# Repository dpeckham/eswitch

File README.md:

# eswitch — eight-channel switching bank

**PROTO-PWR3: bare-board prototype fabrication release.** Shared LM74800-Q1
AUTO/logic protection, with passive raw-battery BYPASS selected by one movable
ATO fuse per channel. BYPASS disconnects the PROFET output and has no series
electronics. Move fuses only with power disconnected.

Open **[redesign/eswitch-simple.kicad_pro](redesign/eswitch-simple.kicad_pro)**.
The **212 × 116 mm**, four-layer ESP32-S3 board retains two banks of four channels
at 26 mm pitch and opposite output edges.

- **[JLCPCB upload ZIP](fab/eswitch-simple-jlcpcb-gerbers.zip)**
- [Order settings](redesign/JLCPCB-ORDER.txt) · [Build/assembly notes](redesign/BUILD.md)
- [Full fabrication package](fab/eswitch-simple-fabrication.zip)
- [Portable KiCad project](fab/eswitch-simple-project.zip)
- [One-board DigiKey upload](fab/eswitch-digikey-qty1.csv)
- [BOM](redesign/bom-draft.csv) · [Partial historical cost estimate](redesign/cost-estimate.json)
- [Top view](fab/board-top.png) · [Bottom view](fab/board-bottom.png)
- [Design overview](redesign/README.md) · [Engineering review](redesign/PROTECTION-REVIEW.md)

Native ERC, DRC, connectivity and schematic parity checks pass. The topology model
checks 52,488 mode/supply combinations and 54 isolation cases. Copper-width and
physical layer-transfer checks cover the shared protection and all channels.

This release permits making **first articles for controlled bench testing**.
40 A continuous operation, +80 V surge survival, pump transients and battery-fault
coordination require hardware validation. It is not an installation qualification.
Firmware is not supplied. Follow BUILD.md for initial current-limited testing.

```sh
just verify    # schematic, topology, saved PCB and copper checks
just package   # matched, checked fabrication/project ZIPs and BOM upload
just render    # current board views
```

Native KiCad is discovered on macOS; override with `KICAD_CLI`/`KICAD_PYTHON`.
`redesign/` is authoritative, `fab/` holds the release, `out/` holds disposable
checks and routing candidates. Earlier releases remain in Git history. Do not
order intermediate `out/redesign` boards. Component pricing is incomplete and
historical, not a current cart quote; F10 fasteners are separate purchases.

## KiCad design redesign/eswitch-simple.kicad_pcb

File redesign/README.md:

# Eight-channel eswitch — PROTO-PWR3

212 × 116 mm, four-layer prototype with shared LM74800-Q1 AUTO/logic protection
and unconditional passive fuse-selected BYPASS. Open `eswitch-simple.kicad_pro`.

The release is for **bare-board first articles and controlled bench testing**.
See [BUILD.md](BUILD.md) for assembly and ordering, and
[PROTECTION-REVIEW.md](PROTECTION-REVIEW.md) for the engineering review and
hardware tests. Neither 40 A continuous operation nor surge survival has been
qualified on hardware. Firmware is not supplied.

## Power paths

```
AUTO:   BATT_RAW -- F10 -- LM74800 cutoff -- shared VS -- PROFET -- ATO fuse -- LOAD
BYPASS: BATT_RAW ----------------------------------------------- ATO fuse -- LOAD
```

One movable ATO fuse per channel, three clips. Pins 1/2/3 are PROFET_OUT/LOAD/RAW.
Move the fuse between AUTO and BYPASS only with power disconnected; remove it for
OFF. BYPASS/OFF disconnects the load from the PROFET output, avoiding body-diode
backfeed. BYPASS has no series electronics and receives raw surges/reversed polarity.

For electronics-fault recovery, disconnect battery and USB, remove F10, move usable
channel fuses to BYPASS, then restore power. All AUTO channels may be lost; no extra
fixed per-channel fuses are required. Upstream-fuse selectivity and uninterrupted
operation are not promised. Shared copper/terminal damage is outside the model.

F10 is a removable Mersen FR14GG50V40 with two MR14SPRING clips and M5 terminals.
F9 remains the 2 A logic fuse. AUTO uses BTS7004 on CH1/2, BTS7008 on CH3–7 and
BTS7002 on CH8. Maximum ATO fuses: **10/10/5/5/5/5/5/20 A**. These are fuse maxima,
not validated continuous channel currents. LEDs show AUTO output voltage; BYPASS
current is not measured. J11–J18 pin 1 is LOAD+, pin 2 is GND. J5 is 3.3 V bench UART.

The common-source protection targets a +80 V, several-second input event using
overvoltage cutoff, not fuse operation or continuous linear clamping. Nominal cutoff
is 16.841 V. The four 200 V and two 60 V MOSFETs use individual gate resistors.
C27 is 1 µF for the parallel-bank charge pump. The existing sense resistance values
remain; R104–R804 use high-power ERJ-PA3 parts for fault-reporting dissipation.

## Verification and fabrication

- Native ERC, PCB DRC, unconnected and schematic-parity checks must all be zero.
- Topology model: 52,488 mode/supply combinations and 54 fault/removal cases.
- `power-copper-review.json`: 60 planar power paths with explicit regression floors.
- `power-transition-review.json`: real pad-layer connections and local via arrays.
- `protection-screen.json` and `sense-screen.json`: reproducible static screens.
- `out/redesign/verification.json`: source hashes and checks for the packaged revision.

The two-layer LOAD corridors, protected supply spine and raw BYPASS feed are
explicitly reserved before routing signals. Geometry checks are not thermal solvers.
Manufacturing uses JLC041622-3313, 2 oz inner and outer copper, filled/capped vias
and 90 Ω USB differential control. Follow `JLCPCB-ORDER.txt` exactly.

```
python3 redesign/generate.py  # explicitly regenerate schematic/BOM after changes
just verify                  # ERC/topology/parity/geometry/physical transitions
just package                 # verified fabrication and portable project ZIPs
just render                  # board views
```

The saved PCB is authoritative. Routing scripts and `out/redesign/protection-*`
files are development history, not alternative ordering files. Some intermediate
candidates intentionally contain errors or disconnected nets. Do not regenerate
placement over the finished board. KiCad's Python environment is required for
layout scripts; `requirements-route-gaps.txt` dependencies live in `out/py39`.

## Procurement and installation

`bom-draft.csv` is the fitted one-board BOM despite its historical filename.
`../fab/eswitch-digikey-qty1.csv` contains exact MPN/quantity upload rows, without
spares. F10 screws, washers and shims are separate mechanical purchases detailed
in BUILD.md. Stock and cart acceptance must be checked when ordering.

`cost-estimate.json` applies historical prices only where known and explicitly
lists unpriced parts. Its subtotal is **not a complete build price or current quote**.
Fabrication, assembly, hardware, shipping and taxes are excluded.

Intended installation: Vatrer 300 Ah LiFePO4, separate Victron Orion XS 12/12-70A
charger branch, 40 A MRBF eswitch feed and 75 A MRBF charger feed. Use 8 AWG copper
positive/negative for the 1 m battery run and 4 mm² positive/negative for the 3 m
pump run. CH1/2 with a provisional 10 A fuse is appropriate for the standard 12 V
Rule 1500 GPH model; confirm the actual pump. Direct-battery fault coordination,
thermal limits, pump transients and surge performance remain hardware tests.

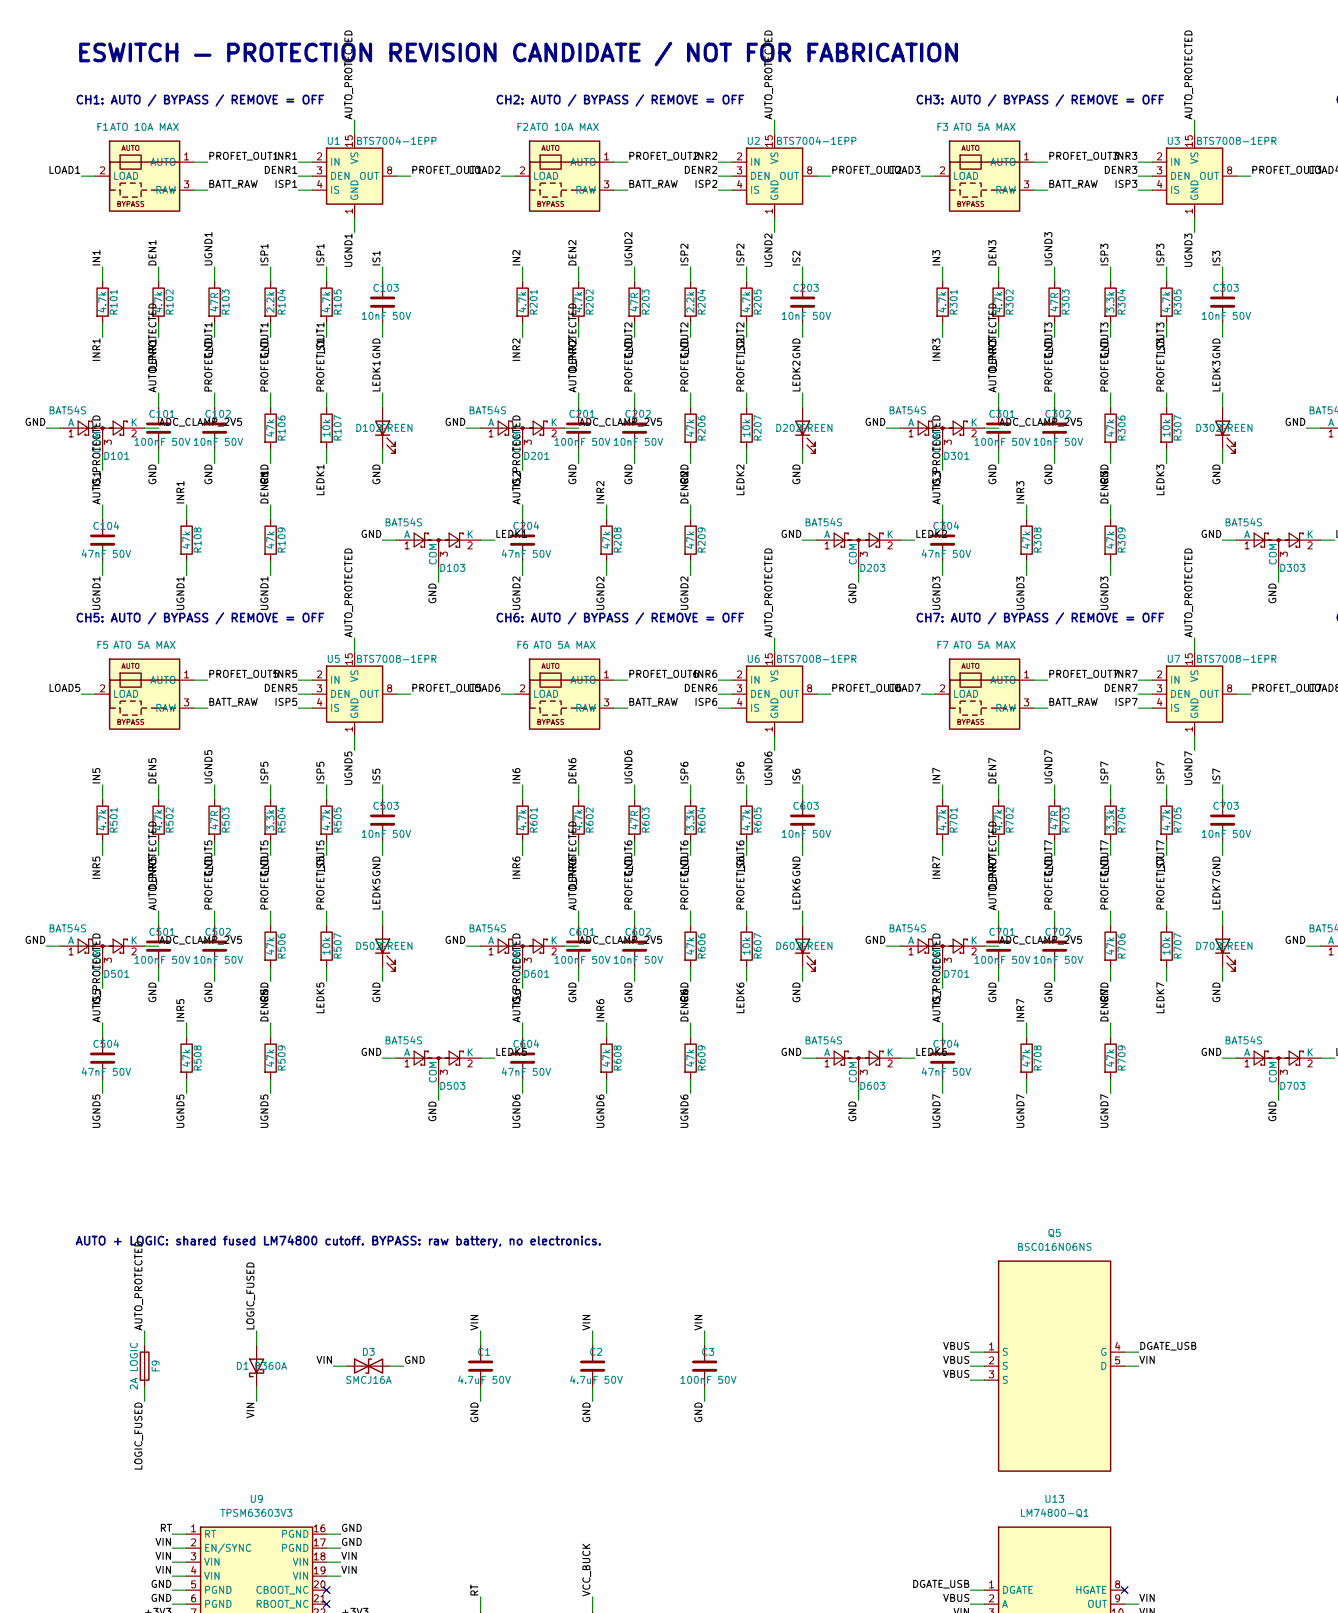
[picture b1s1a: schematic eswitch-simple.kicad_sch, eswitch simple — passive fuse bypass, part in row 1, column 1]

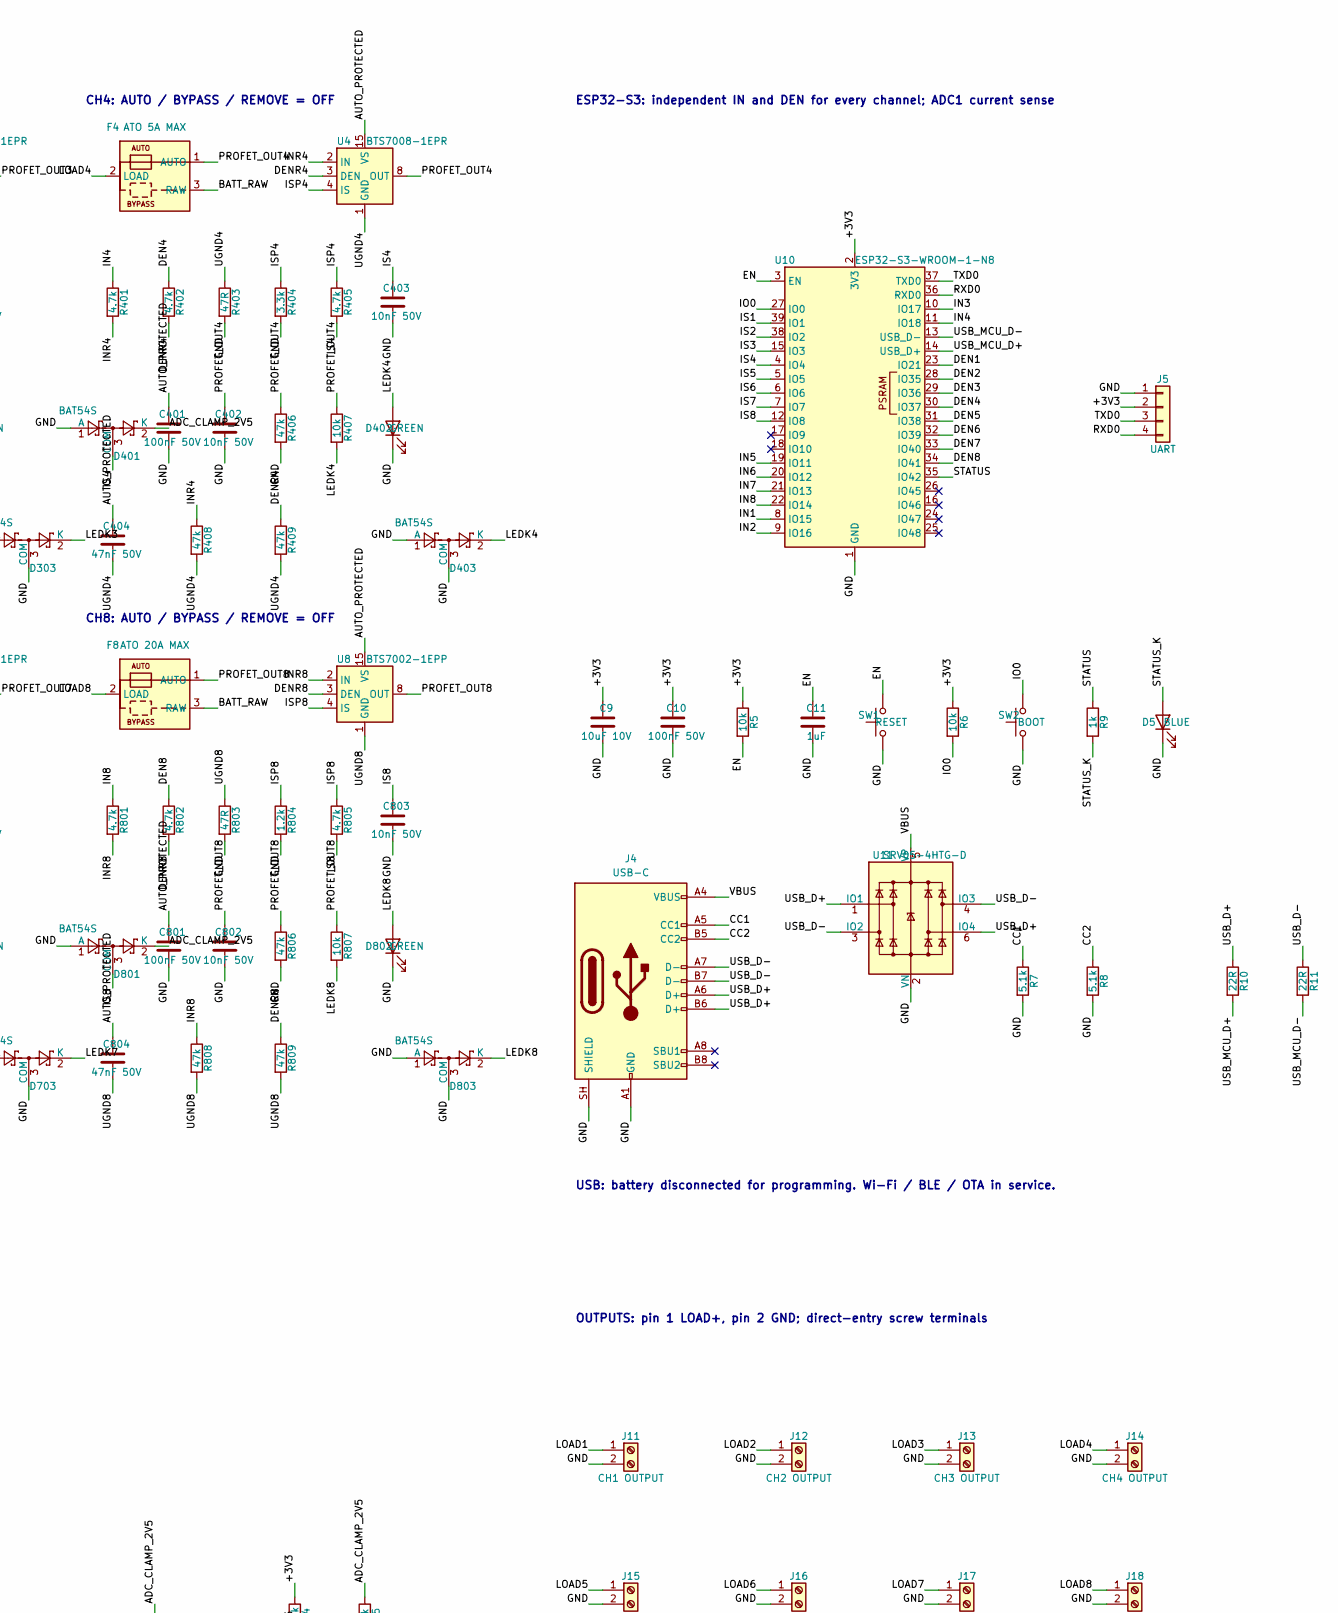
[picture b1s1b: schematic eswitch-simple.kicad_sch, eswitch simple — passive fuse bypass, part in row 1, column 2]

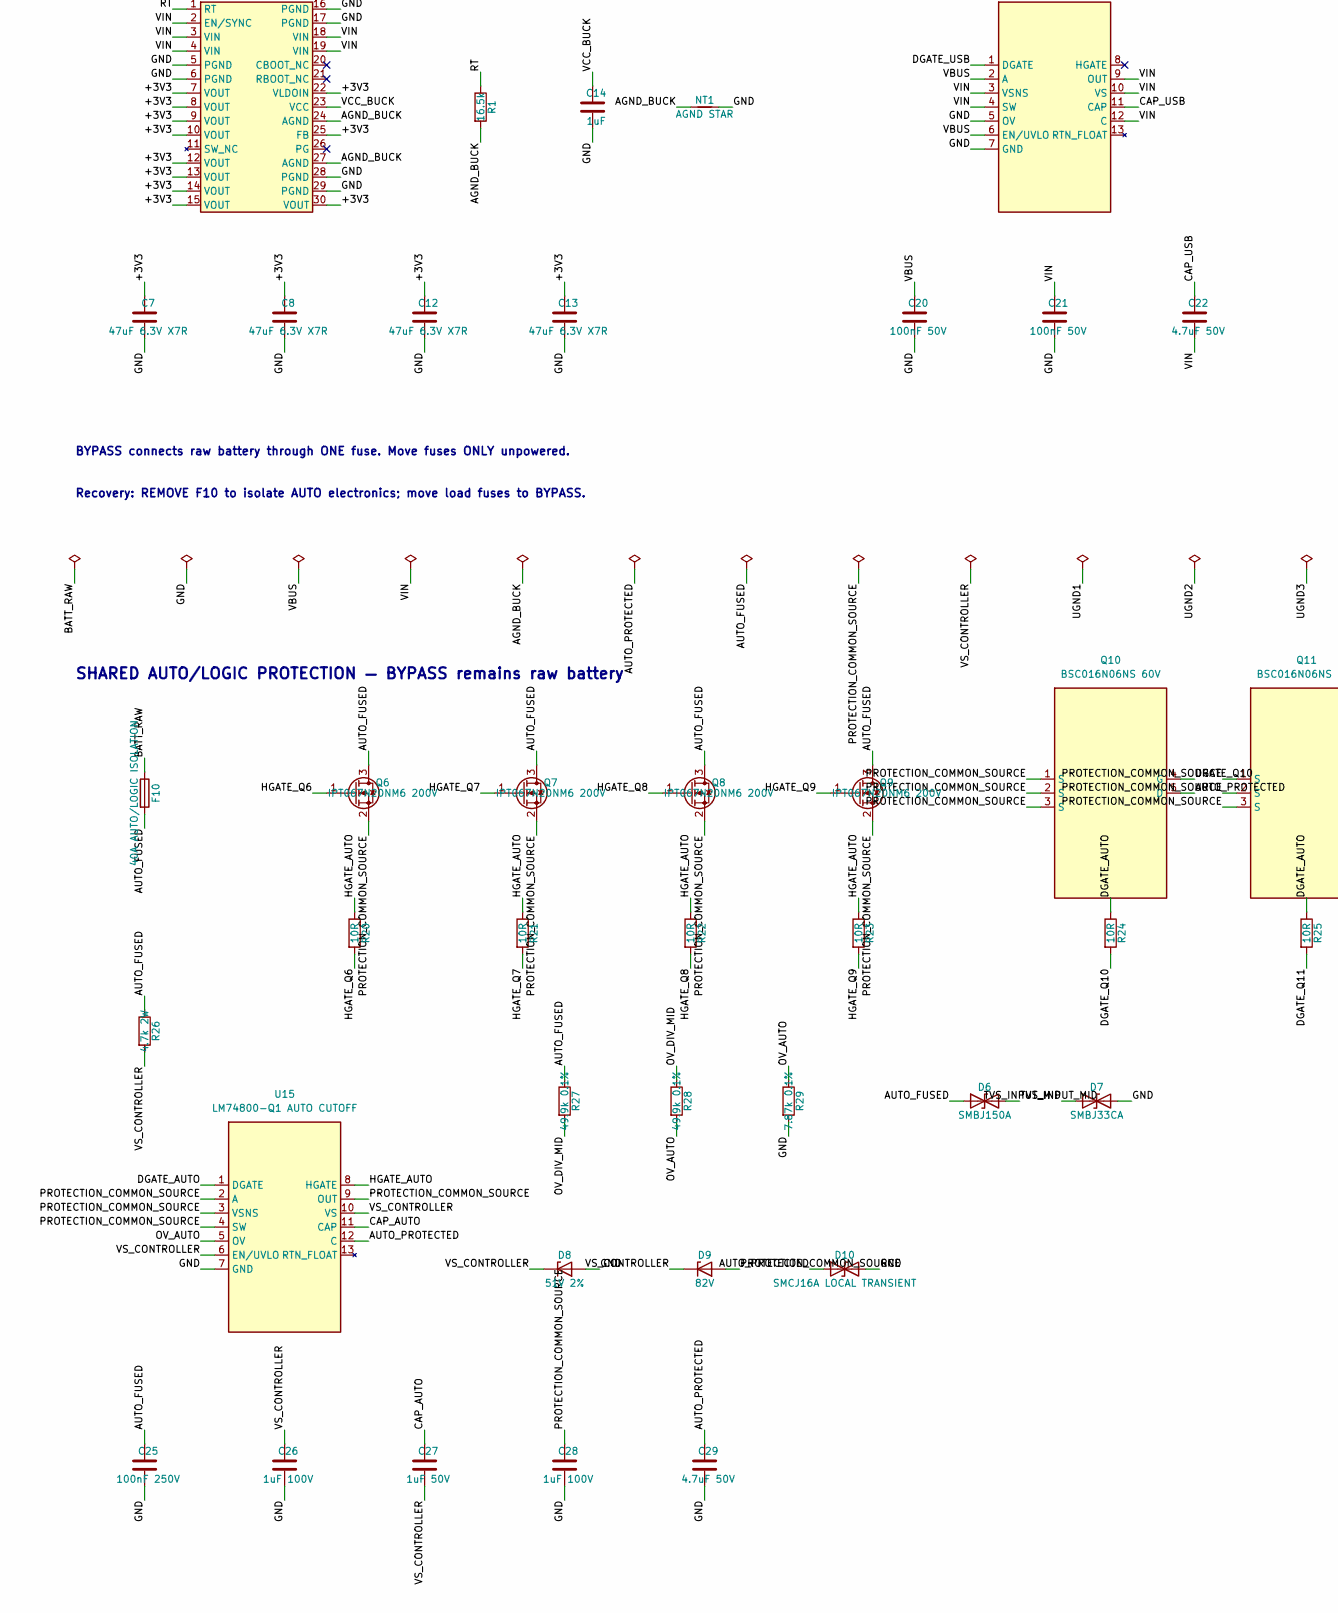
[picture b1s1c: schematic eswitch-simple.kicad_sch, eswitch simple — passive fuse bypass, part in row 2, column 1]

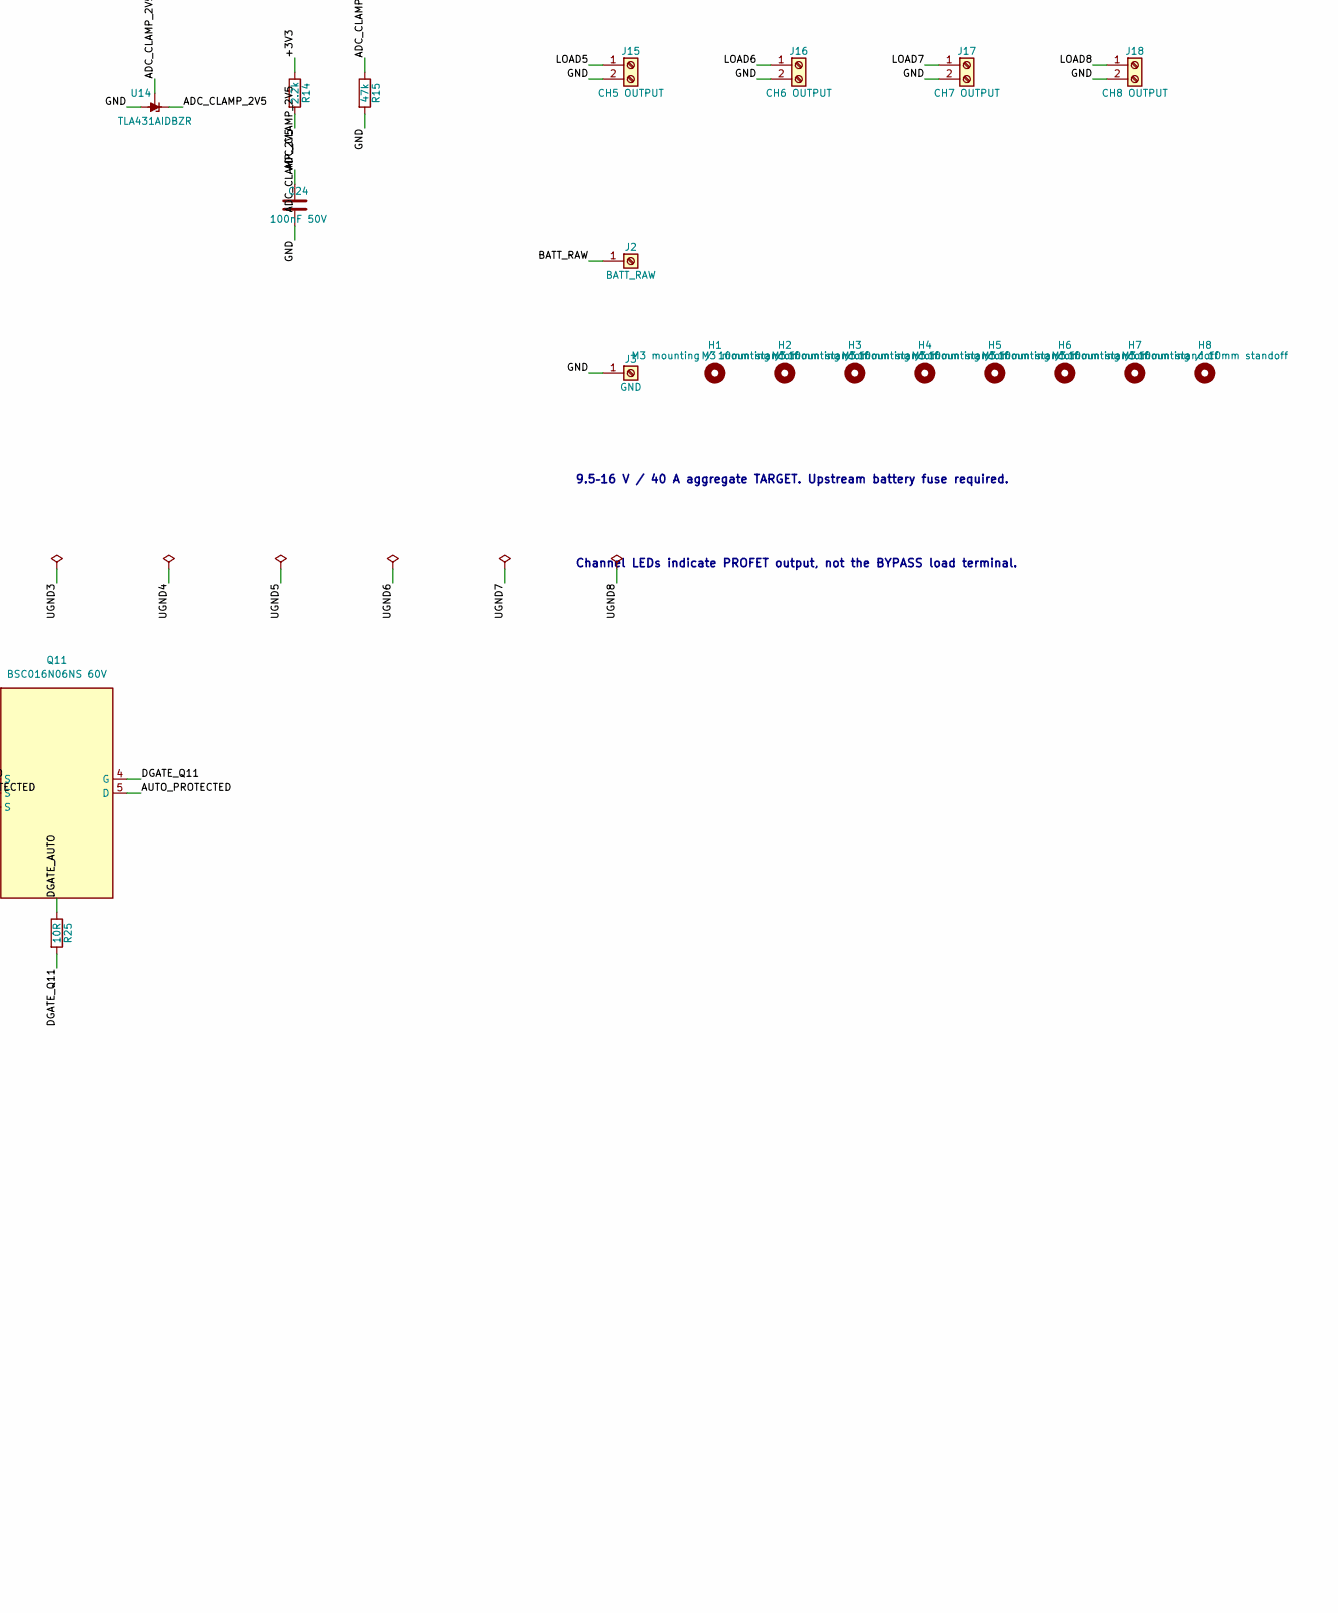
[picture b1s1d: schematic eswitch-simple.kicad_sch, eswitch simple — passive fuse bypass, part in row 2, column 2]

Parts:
C1, C2, C22, C29: 4.7uF 50V; C_1210_3225Metric; MPN GRM32ER71H475KA88L
C3, C10, C20, C21, C24, C101, C201, C301, C401, C501, C601, C701, C801: 100nF 50V; C_0805_2012Metric; MPN CL21B104KBCNNNC
C7, C8, C12, C13: 47uF 6.3V X7R; C_1210_3225Metric; MPN GCM32ER70J476KE19L
C9: 10uF 10V; C_0805_2012Metric; MPN CC0805KKX5R6BB106
C11, C14: 1uF; C_0603_1608Metric; MPN CC0603KRX7R7BB105
C25: 100nF 250V; C_1210_3225Metric; MPN C3225X7R2E104K200AA
C26, C28: 1uF 100V; C_1210_3225Metric; MPN GRM32CR72A105KA35L
C27: 1uF 50V; C_0805_2012Metric; MPN GRM21BR71H105KA12L
C102, C103, C202, C203, C302, C303, C402, C403, C502, C503, C602, C603, C702, C703, C802, C803: 10nF 50V; C_0805_2012Metric; MPN CL21B103KBANNNC
C104, C204, C304, C404, C504, C604, C704, C804: 47nF 50V; C_0805_2012Metric; MPN CL21B473KBCNNNC
D1: B360A; D_SMA; MPN B360A-13-F
D3: SMCJ16A; D_SMC; MPN SMCJ16A
D5: BLUE; LED_0603_1608Metric; MPN 150060BS75000
D6: SMBJ150A; D_SMB; MPN SMBJ150A
D7: SMBJ33CA; D_SMB; MPN SMBJ33CA
D8: 51V 2%; D_SMA; MPN BZG03B51-M3_A-08
D9: 82V; D_SMA; MPN BZG03C82-M3_A-08
D10: SMCJ16A LOCAL TRANSIENT; D_SMC; MPN SMCJ16A
D101, D103, D201, D203, D301, D303, D401, D403, D501, D503, D601, D603, D701, D703, D801, D803: BAT54S; SOT-23; MPN BAT54S-QR
D102, D202, D302, D402, D502, D602, D702, D802: GREEN; LED_0603_1608Metric; MPN 150060GS75000
F1, F2: ATO 10A MAX; Fuseholder_ATO_3pos_Keystone_3557; MPN 3557
F3, F4, F5, F6, F7: ATO 5A MAX; Fuseholder_ATO_3pos_Keystone_3557; MPN 3557
F8: ATO 20A MAX; Fuseholder_ATO_3pos_Keystone_3557; MPN 3557
F9: 2A LOGIC; Fuse_1206_3216Metric; MPN 0466002.NR
F10: 40A AUTO/LOGIC ISOLATION; Fuse_Mersen_14x51_MR14_Wuerth_M5; MPN FR14GG50V40
H1, H2, H3, H4, H5, H6, H7, H8: M3 mounting / 10mm standoff; MountingHole_3.2mm_M3; MPN R30-1001002
J2: BATT_RAW; ScrewTerminal_Wuerth_74650195_M5; MPN 74650195
J3: GND; ScrewTerminal_Wuerth_74650195_M5; MPN 74650195
J4: USB-C; USB4105_NPTH_0p2; MPN USB4105-GF-A
J5: UART; PinHeader_1x04_P2.54mm_Vertical; MPN 61300411121
J11: CH1 OUTPUT; TerminalBlock_1x02_P7.62mm_Wuerth_2184; MPN 691218410002
J12: CH2 OUTPUT; TerminalBlock_1x02_P7.62mm_Wuerth_2184; MPN 691218410002
J13: CH3 OUTPUT; TerminalBlock_1x02_P7.62mm_Wuerth_2184; MPN 691218410002
J14: CH4 OUTPUT; TerminalBlock_1x02_P7.62mm_Wuerth_2184; MPN 691218410002
J15: CH5 OUTPUT; TerminalBlock_1x02_P7.62mm_Wuerth_2184; MPN 691218410002
J16: CH6 OUTPUT; TerminalBlock_1x02_P7.62mm_Wuerth_2184; MPN 691218410002
J17: CH7 OUTPUT; TerminalBlock_1x02_P7.62mm_Wuerth_2184; MPN 691218410002
J18: CH8 OUTPUT; TerminalBlock_1x02_P7.62mm_Wuerth_2184; MPN 691218410002
NT1: AGND STAR; NetTie-2_SMD_Pad0.5mm
Q5: BSC016N06NS; Infineon_PG-TDSON-8_6.15x5.15mm; MPN BSC016N06NSATMA1
Q6, Q7, Q8, Q9: IPT067N20NM6 200V; Infineon_PG-HSOF-8-1; MPN IPT067N20NM6ATMA1
Q10, Q11: BSC016N06NS 60V; Infineon_PG-TDSON-8_6.15x5.15mm; MPN BSC016N06NSATMA1
R1: 16.5k; R_0603_1608Metric; MPN RC0603FR-0716K5L
R5, R6, R107, R207, R307, R407, R507, R607, R707, R807: 10k; R_0603_1608Metric; MPN RC0603FR-0710KL
R7, R8: 5.1k; R_0603_1608Metric; MPN ERJ-3EKF5101V
R9: 1k; R_0603_1608Metric; MPN RC0603FR-071KL
R10, R11: 22R; R_0603_1608Metric; MPN ERJ-3EKF22R0V
R14: 2.2k; R_0603_1608Metric; MPN RC0603FR-072K2L
R15, R106, R108, R109, R206, R208, R209, R306, R308, R309, R406, R408, R409, R506, R508, R509, R606, R608, R609, R706, R708, R709, R806, R808, R809: 47k; R_0603_1608Metric; MPN RC0603FR-0747KL
R20, R21, R22, R23, R24, R25: 10R; R_0805_2012Metric; MPN RC0805FR-0710RL
R26: 4.7k 2W; R_Axial_DIN0411_L9.9mm_D3.6mm_P15.24mm_Horizontal; MPN PR02000204701JA100
R27, R28: 49.9k 0.1%; R_0805_2012Metric; MPN RT0805BRD0749K9L
R29: 7.87k 0.1%; R_0805_2012Metric; MPN RT0805BRD077K87L
R101, R102, R105, R201, R202, R205, R301, R302, R305, R401, R402, R405, R501, R502, R505, R601, R602, R605, R701, R702, R705, R801, R802, R805: 4.7k; R_0603_1608Metric; MPN RC0603FR-074K7L
R103, R203, R303, R403, R503, R603, R703, R803: 47R; R_0805_2012Metric; MPN RC0805FR-0747RL
R104, R204: 2.2k; R_0603_1608Metric; MPN ERJ-PA3F2201V
R304, R404, R504, R604, R704: 3.3k; R_0603_1608Metric; MPN ERJ-PA3F3301V
R804: 1.2k; R_0603_1608Metric; MPN ERJ-PA3F1201V
SW1: RESET; SW_SPST_PTS645Sx43SMTR92; MPN PTS645SM43SMTR92 LFS
SW2: BOOT; SW_SPST_PTS645Sx43SMTR92; MPN PTS645SM43SMTR92 LFS
U1, U2: BTS7004-1EPP; Infineon_PG-TSDSO-14-22; MPN BTS70041EPPXUMA1
U3, U4, U5, U6, U7: BTS7008-1EPR; Infineon_PG-TSDSO-14-22; MPN BTS70081EPRXUMA1
U8: BTS7002-1EPP; Infineon_PG-TSDSO-14-22; MPN BTS70021EPPXUMA1
U9: TPSM63603V3; TI_RDH0030A_TPSM63603; MPN TPSM63603V3RDHR
U10: ESP32-S3-WROOM-1-N8; ESP32-S3-WROOM-1_Edge; MPN ESP32-S3-WROOM-1-N8
U11: SRV05-4HTG-D; SOT-23-6; MPN SRV05-4HTG-D
U13: LM74800-Q1; WSON-12-1EP_3x3mm_P0.5mm_EP1.5x2.5mm; MPN LM74800QDRRRQ1
U14: TLA431AIDBZR; SOT-23; MPN TLA431AIDBZR
U15: LM74800-Q1 AUTO CUTOFF; WSON-12-1EP_3x3mm_P0.5mm_EP1.5x2.5mm; MPN LM74800QDRRRQ1

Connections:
/+3V3: C7.1, C8.1, C9.1, C10.1, C12.1, C13.1, J5.2, R5.1, R6.1, R14.1, U9.7 (VOUT), U9.8 (VOUT), U9.9 (VOUT), U9.10 (VOUT), U9.12 (VOUT), U9.13 (VOUT), U9.14 (VOUT), U9.15 (VOUT), U9.22 (VLDOIN), U9.25 (FB), U9.30 (VOUT), U10.2 (3V3)
/ADC_CLAMP_2V5: C24.1, D101.2 (K), D201.2 (K), D301.2 (K), D401.2 (K), D501.2 (K), D601.2 (K), D701.2 (K), D801.2 (K), R14.2, R15.1, U14.1 (K), U14.2 (REF)
/AGND_BUCK: NT1.1, R1.2, U9.24 (AGND), U9.27 (AGND)
/AUTO_FUSED: C25.1, D6.1 (A1), F10.2, Q6.3 (D), Q7.3 (D), Q8.3 (D), Q9.3 (D), R26.1, R27.1
/AUTO_PROTECTED: C29.1, C101.1, C104.1, C201.1, C204.1, C301.1, C304.1, C401.1, C404.1, C501.1, C504.1, C601.1, C604.1, C701.1, C704.1, C801.1, C804.1, D10.1 (A1), F9.1, Q10.5 (D), Q11.5 (D), U1.15 (VS), U2.15 (VS), U3.15 (VS), U4.15 (VS), U5.15 (VS), U6.15 (VS), U7.15 (VS), U8.15 (VS), U15.12 (C)
/BATT_RAW: F1.3 (RAW), F2.3 (RAW), F3.3 (RAW), F4.3 (RAW), F5.3 (RAW), F6.3 (RAW), F7.3 (RAW), F8.3 (RAW), F10.1, J2.1
/CAP_AUTO: C27.1, U15.11 (CAP)
/CAP_USB: C22.1, U13.11 (CAP)
/CC1: J4.A5 (CC1), R7.1
/CC2: J4.B5 (CC2), R8.1
/DEN1: R102.1, U10.23 (IO21)
/DEN2: R202.1, U10.28 (IO35)
/DEN3: R302.1, U10.29 (IO36)
/DEN4: R402.1, U10.30 (IO37)
/DEN5: R502.1, U10.31 (IO38)
/DEN6: R602.1, U10.32 (IO39)
/DEN7: R702.1, U10.33 (IO40)
/DEN8: R802.1, U10.34 (IO41)
/DENR1: R102.2, R109.1, U1.3 (DEN)
/DENR2: R202.2, R209.1, U2.3 (DEN)
/DENR3: R302.2, R309.1, U3.3 (DEN)
/DENR4: R402.2, R409.1, U4.3 (DEN)
/DENR5: R502.2, R509.1, U5.3 (DEN)
/DENR6: R602.2, R609.1, U6.3 (DEN)
/DENR7: R702.2, R709.1, U7.3 (DEN)
/DENR8: R802.2, R809.1, U8.3 (DEN)
/DGATE_AUTO: R24.1, R25.1, U15.1 (DGATE)
/DGATE_Q10: Q10.4 (G), R24.2
/DGATE_Q11: Q11.4 (G), R25.2
/DGATE_USB: Q5.4 (G), U13.1 (DGATE)
/EN: C11.1, R5.2, SW1.2, U10.3 (EN)
/GND: C1.2, C2.2, C3.2, C7.2, C8.2, C9.2, C10.2, C11.2, C12.2, C13.2, C14.2, C20.2, C21.2, C24.2, C25.2, C26.2, C28.2, C29.2, C101.2, C102.2, C103.2, C201.2, C202.2, C203.2, C301.2, C302.2, C303.2, C401.2, C402.2, C403.2, C501.2, C502.2, C503.2, C601.2, C602.2, C603.2, C701.2, C702.2, C703.2, C801.2, C802.2, C803.2, D3.2 (A2), D5.1 (K), D7.2 (A2), D8.2 (A), D10.2 (A2), D101.1 (A), D102.1 (K), D103.1 (A), D103.3 (COM), D201.1 (A), D202.1 (K), D203.1 (A), D203.3 (COM), D301.1 (A), D302.1 (K), D303.1 (A), D303.3 (COM), D401.1 (A), D402.1 (K), D403.1 (A), D403.3 (COM), D501.1 (A), D502.1 (K), D503.1 (A), D503.3 (COM), D601.1 (A), D602.1 (K), D603.1 (A), D603.3 (COM), D701.1 (A), D702.1 (K), D703.1 (A), D703.3 (COM), D801.1 (A), D802.1 (K), D803.1 (A), D803.3 (COM), J3.1, J4.A1 (GND), J4.A12 (GND), J4.B1 (GND), J4.B12 (GND), J4.SH (SHIELD), J5.1, J11.2, J12.2, J13.2, J14.2, J15.2, J16.2, J17.2, J18.2, NT1.2, R7.2, R8.2, R15.2, R29.2, R103.2, R104.2, R106.2, R203.2, R204.2, R206.2, R303.2, R304.2, R306.2, R403.2, R404.2, R406.2, R503.2, R504.2, R506.2, R603.2, R604.2, R606.2, R703.2, R704.2, R706.2, R803.2, R804.2, R806.2, SW1.1, SW2.1, U9.5 (PGND), U9.6 (PGND), U9.16 (PGND), U9.17 (PGND), U9.28 (PGND), U9.29 (PGND), U10.1 (GND), U10.40 (GND), U10.41 (GND), U11.2 (VN), U13.5 (OV), U13.7 (GND), U14.3 (A), U15.7 (GND)
/HGATE_AUTO: R20.1, R21.1, R22.1, R23.1, U15.8 (HGATE)
/HGATE_Q6: Q6.1 (G), R20.2
/HGATE_Q7: Q7.1 (G), R21.2
/HGATE_Q8: Q8.1 (G), R22.2
/HGATE_Q9: Q9.1 (G), R23.2
/IN1: R101.1, U10.8 (IO15)
/IN2: R201.1, U10.9 (IO16)
/IN3: R301.1, U10.10 (IO17)
/IN4: R401.1, U10.11 (IO18)
/IN5: R501.1, U10.19 (IO11)
/IN6: R601.1, U10.20 (IO12)
/IN7: R701.1, U10.21 (IO13)
/IN8: R801.1, U10.22 (IO14)
/INR1: R101.2, R108.1, U1.2 (IN)
/INR2: R201.2, R208.1, U2.2 (IN)
/INR3: R301.2, R308.1, U3.2 (IN)
/INR4: R401.2, R408.1, U4.2 (IN)
/INR5: R501.2, R508.1, U5.2 (IN)
/INR6: R601.2, R608.1, U6.2 (IN)
/INR7: R701.2, R708.1, U7.2 (IN)
/INR8: R801.2, R808.1, U8.2 (IN)
/IO0: R6.2, SW2.2, U10.27 (IO0)
/IS1: C103.1, D101.3 (COM), R105.2, U10.39 (IO1)
/IS2: C203.1, D201.3 (COM), R205.2, U10.38 (IO2)
/IS3: C303.1, D301.3 (COM), R305.2, U10.15 (IO3)
/IS4: C403.1, D401.3 (COM), R405.2, U10.4 (IO4)
/IS5: C503.1, D501.3 (COM), R505.2, U10.5 (IO5)
/IS6: C603.1, D601.3 (COM), R605.2, U10.6 (IO6)
/IS7: C703.1, D701.3 (COM), R705.2, U10.7 (IO7)
/IS8: C803.1, D801.3 (COM), R805.2, U10.12 (IO8)
/ISP1: R104.1, R105.1, U1.4 (IS)
/ISP2: R204.1, R205.1, U2.4 (IS)
/ISP3: R304.1, R305.1, U3.4 (IS)
/ISP4: R404.1, R405.1, U4.4 (IS)
/ISP5: R504.1, R505.1, U5.4 (IS)
/ISP6: R604.1, R605.1, U6.4 (IS)
/ISP7: R704.1, R705.1, U7.4 (IS)
/ISP8: R804.1, R805.1, U8.4 (IS)
/LEDK1: D102.2 (A), D103.2 (K), R107.2
/LEDK2: D202.2 (A), D203.2 (K), R207.2
/LEDK3: D302.2 (A), D303.2 (K), R307.2
/LEDK4: D402.2 (A), D403.2 (K), R407.2
/LEDK5: D502.2 (A), D503.2 (K), R507.2
/LEDK6: D602.2 (A), D603.2 (K), R607.2
/LEDK7: D702.2 (A), D703.2 (K), R707.2
/LEDK8: D802.2 (A), D803.2 (K), R807.2
/LOAD1: F1.2 (LOAD), J11.1
/LOAD2: F2.2 (LOAD), J12.1
/LOAD3: F3.2 (LOAD), J13.1
/LOAD4: F4.2 (LOAD), J14.1
/LOAD5: F5.2 (LOAD), J15.1
/LOAD6: F6.2 (LOAD), J16.1
/LOAD7: F7.2 (LOAD), J17.1
/LOAD8: F8.2 (LOAD), J18.1
/LOGIC_FUSED: D1.2 (A), F9.2
/OV_AUTO: R28.2, R29.1, U15.5 (OV)
/OV_DIV_MID: R27.2, R28.1
/PROFET_OUT1: C102.1, F1.1 (AUTO), R106.1, R107.1, U1.8 (OUT), U1.9 (OUT), U1.10 (OUT), U1.12 (OUT), U1.13 (OUT), U1.14 (OUT)
/PROFET_OUT2: C202.1, F2.1 (AUTO), R206.1, R207.1, U2.8 (OUT), U2.9 (OUT), U2.10 (OUT), U2.12 (OUT), U2.13 (OUT), U2.14 (OUT)
/PROFET_OUT3: C302.1, F3.1 (AUTO), R306.1, R307.1, U3.8 (OUT), U3.9 (OUT), U3.10 (OUT), U3.12 (OUT), U3.13 (OUT), U3.14 (OUT)
/PROFET_OUT4: C402.1, F4.1 (AUTO), R406.1, R407.1, U4.8 (OUT), U4.9 (OUT), U4.10 (OUT), U4.12 (OUT), U4.13 (OUT), U4.14 (OUT)
/PROFET_OUT5: C502.1, F5.1 (AUTO), R506.1, R507.1, U5.8 (OUT), U5.9 (OUT), U5.10 (OUT), U5.12 (OUT), U5.13 (OUT), U5.14 (OUT)
/PROFET_OUT6: C602.1, F6.1 (AUTO), R606.1, R607.1, U6.8 (OUT), U6.9 (OUT), U6.10 (OUT), U6.12 (OUT), U6.13 (OUT), U6.14 (OUT)
/PROFET_OUT7: C702.1, F7.1 (AUTO), R706.1, R707.1, U7.8 (OUT), U7.9 (OUT), U7.10 (OUT), U7.12 (OUT), U7.13 (OUT), U7.14 (OUT)
/PROFET_OUT8: C802.1, F8.1 (AUTO), R806.1, R807.1, U8.8 (OUT), U8.9 (OUT), U8.10 (OUT), U8.12 (OUT), U8.13 (OUT), U8.14 (OUT)
/PROTECTION_COMMON_SOURCE: C28.1, D9.2 (A), Q6.2 (S), Q7.2 (S), Q8.2 (S), Q9.2 (S), Q10.1 (S), Q10.2 (S), Q10.3 (S), Q11.1 (S), Q11.2 (S), Q11.3 (S), U15.2 (A), U15.3 (VSNS), U15.4 (SW), U15.9 (OUT)
/RT: R1.1, U9.1 (RT)
/RXD0: J5.4, U10.36 (RXD0)
/STATUS: R9.1, U10.35 (IO42)
/STATUS_K: D5.2 (A), R9.2
/TVS_INPUT_MID: D6.2 (A2), D7.1 (A1)
/TXD0: J5.3, U10.37 (TXD0)
/UGND1: C104.2, R103.1, R108.2, R109.2, U1.1 (GND)
/UGND2: C204.2, R203.1, R208.2, R209.2, U2.1 (GND)
/UGND3: C304.2, R303.1, R308.2, R309.2, U3.1 (GND)
/UGND4: C404.2, R403.1, R408.2, R409.2, U4.1 (GND)
/UGND5: C504.2, R503.1, R508.2, R509.2, U5.1 (GND)
/UGND6: C604.2, R603.1, R608.2, R609.2, U6.1 (GND)
/UGND7: C704.2, R703.1, R708.2, R709.2, U7.1 (GND)
/UGND8: C804.2, R803.1, R808.2, R809.2, U8.1 (GND)
/USB_D+: J4.A6 (D+), J4.B6 (D+), R10.1, U11.1 (IO1), U11.6 (IO4)
/USB_D-: J4.A7 (D-), J4.B7 (D-), R11.1, U11.3 (IO2), U11.4 (IO3)
/USB_MCU_D+: R10.2, U10.14 (USB_D+)
/USB_MCU_D-: R11.2, U10.13 (USB_D-)
/VBUS: C20.1, J4.A4 (VBUS), J4.A9 (VBUS), J4.B4 (VBUS), J4.B9 (VBUS), Q5.1 (S), Q5.2 (S), Q5.3 (S), U11.5 (VP), U13.2 (A), U13.6 (EN/UVLO)
/VCC_BUCK: C14.1, U9.23 (VCC)
/VIN: C1.1, C2.1, C3.1, C21.1, C22.2, D1.1 (K), D3.1 (A1), Q5.5 (D), U9.2 (EN/SYNC), U9.3 (VIN), U9.4 (VIN), U9.18 (VIN), U9.19 (VIN), U13.3 (VSNS), U13.4 (SW), U13.9 (OUT), U13.10 (VS), U13.12 (C)
/VS_CONTROLLER: C26.1, C27.2, D8.1 (K), D9.1 (K), R26.2, U15.6 (EN/UVLO), U15.10 (VS)

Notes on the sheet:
ESWITCH — PROTECTION REVISION CANDIDATE / NOT FOR FABRICATION
ESP32-S3: independent IN and DEN for every channel; ADC1 current sense
USB: battery disconnected for programming. Wi-Fi / BLE / OTA in service.
AUTO + LOGIC: shared fused LM74800 cutoff. BYPASS: raw battery, no electronics.
OUTPUTS: pin 1 LOAD+, pin 2 GND; direct-entry screw terminals
9.5–16 V / 40 A aggregate TARGET. Upstream battery fuse required.
BYPASS connects raw battery through ONE fuse. Move fuses ONLY unpowered.
Recovery: REMOVE F10 to isolate AUTO electronics; move load fuses to BYPASS.
SHARED AUTO/LOGIC PROTECTION — BYPASS remains raw battery
Channel LEDs indicate PROFET output, not the BYPASS load terminal.
CH1: AUTO / BYPASS / REMOVE = OFF
CH2: AUTO / BYPASS / REMOVE = OFF
CH3: AUTO / BYPASS / REMOVE = OFF
CH4: AUTO / BYPASS / REMOVE = OFF
CH5: AUTO / BYPASS / REMOVE = OFF
CH6: AUTO / BYPASS / REMOVE = OFF
CH7: AUTO / BYPASS / REMOVE = OFF
CH8: AUTO / BYPASS / REMOVE = OFF

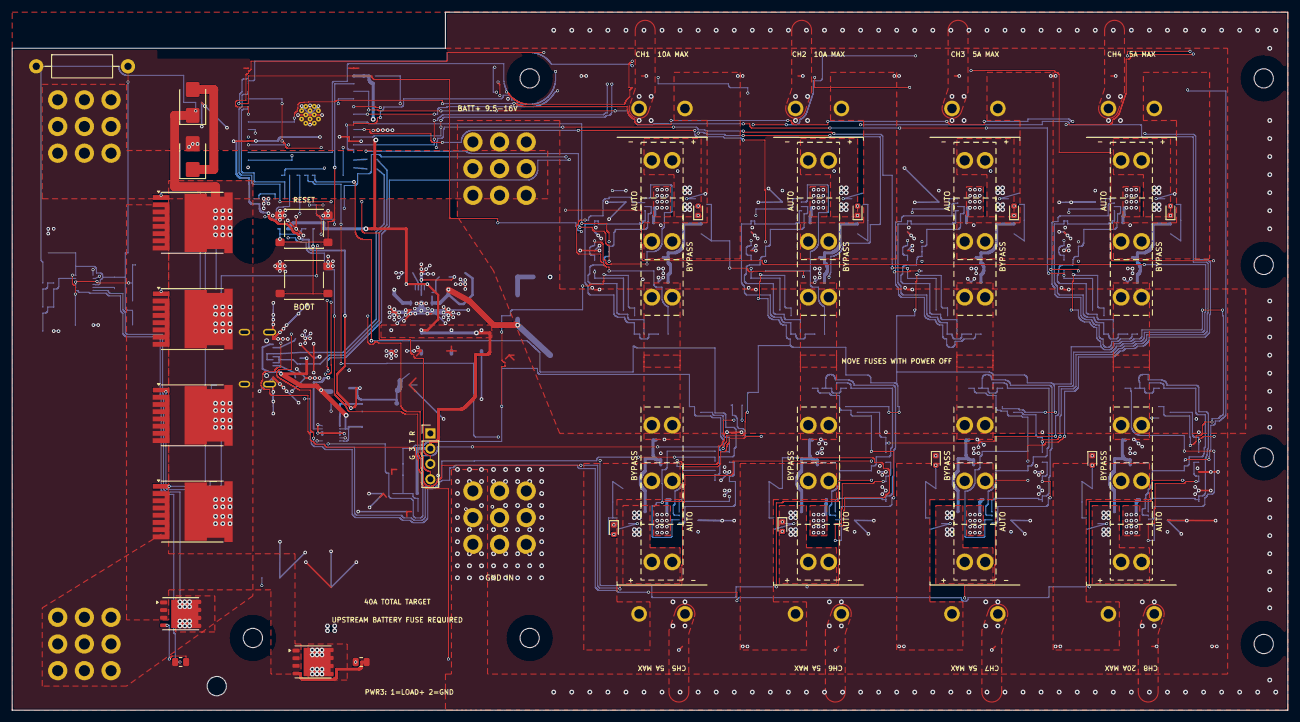
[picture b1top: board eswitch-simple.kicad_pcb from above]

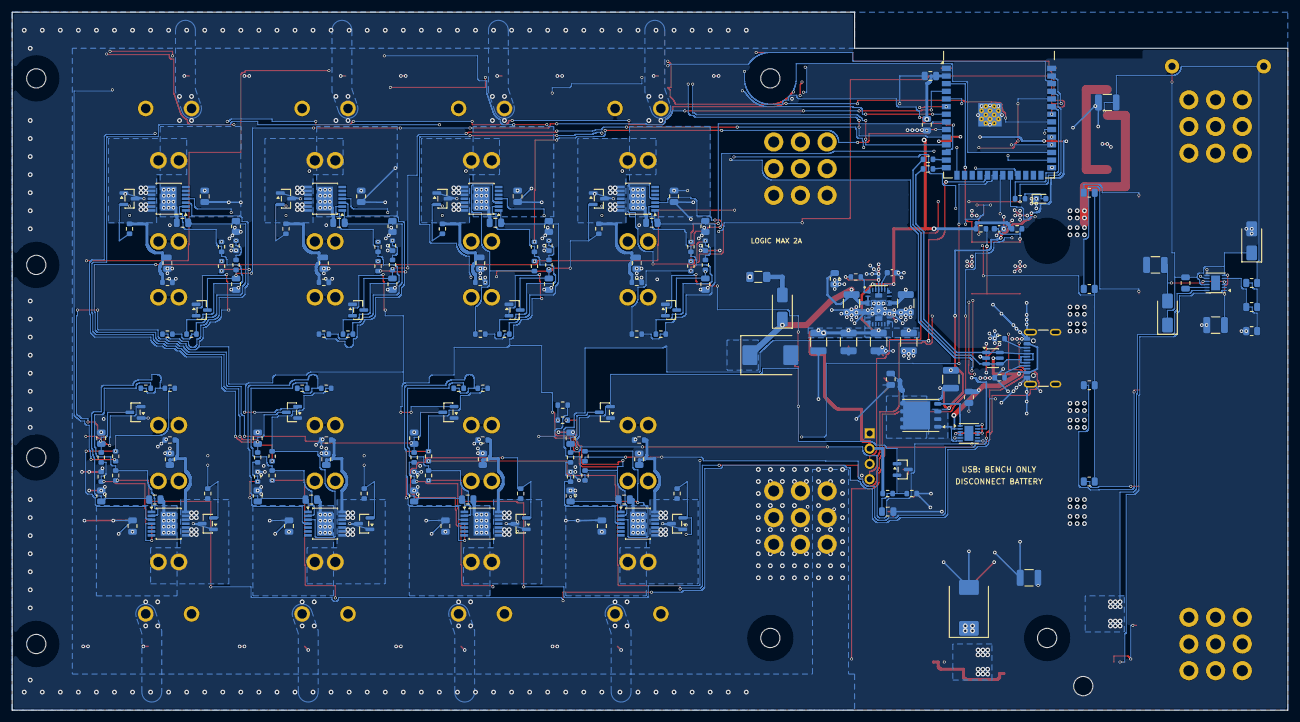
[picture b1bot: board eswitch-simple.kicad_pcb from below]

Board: 4 copper layers, 212.0 x 116.0 mm, 230 parts (181 on the bottom side), 120 nets.

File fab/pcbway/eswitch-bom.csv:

Item #,Designator,Qty,Manufacturer,Mfg Part #,Description / Value,Package/Footprint,Type,Your Instructions / Notes
1,"C1,C2",2,Murata,GRM32ER71H475KA88L,4.7uF 50V,1210,SMD,
2,C3,1,Samsung Electro-Mechanics,CL10B104KB8NNNC,100nF 50V,0603,SMD,
3,C4,1,Samsung Electro-Mechanics,CL10B104KB8NNNC,100nF 25V,0603,SMD,
4,C5,1,Samsung Electro-Mechanics,CL10B273KB8NNNC,27nF,0603,SMD,
5,C6,1,Samsung Electro-Mechanics,CL10C151JB8NNNC,150pF,0603,SMD,
6,"C7,C8",2,Murata,GRM32ER71A226KE20L,22uF 10V,1210,SMD,
7,C9,1,Samsung Electro-Mechanics,CL21A106KPFNNNE,10uF 10V,0805,SMD,
8,C10,1,Samsung Electro-Mechanics,CL10B104KB8NNNC,100nF,0603,SMD,
9,C11,1,Samsung Electro-Mechanics,CL10B105KO8NNNC,1uF,0603,SMD,
10,"C101,C201,C301,C401,C501,C601,C701,C801",8,Samsung Electro-Mechanics,CL21B104KBCNNNC,100nF 50V,0805,SMD,CVS
11,"C102,C202,C302,C402,C502,C602,C702,C802",8,Samsung Electro-Mechanics,CL21B103KBANNNC,10nF 50V,0805,SMD,COUT
12,"C103,C203,C303,C403,C503,C603,C703,C803",8,Samsung Electro-Mechanics,CL10C221JB8NNNC,220pF 50V,0603,SMD,CSENSE
13,"D1,D2,D4",3,Diodes Incorporated,B360-13-F,SS36,SMA,SMD,"12V -> VIN,USB -> VIN,catch diode"
14,D3,1,Littelfuse,SMBJ26A,SMBJ26A,SMB,SMD,bus TVS
15,D5,1,Wurth Elektronik,150060BS75000,BLUE,LED_0603,SMD,status LED IO41
16,"D101,D201,D301,D401,D501,D601,D701,D801",8,Nexperia,"BAT54S,215",BAT54S,SOT-23,SMD,ADC clamp
17,"D102,D202,D302,D402,D502,D602,D702,D802",8,Wurth Elektronik,150060GS75000,GREEN,LED_0603,SMD,load ON indicator
18,"F1,F2",2,Keystone Electronics,3557,ATO 10A,Fuseholder_ATO_3pos_Keystone_3557,Through-hole,"3 clips per position; CH1 10 A; AUTO: fuse in COM-SW; BYPASS: fuse in COM-LOAD,3 clips per position; CH2 10 A; AUTO: fuse in COM-SW; BYPASS: fuse in COM-LOAD"
19,"F3,F4,F5,F6,F7",5,Keystone Electronics,3557,ATO 5A,Fuseholder_ATO_3pos_Keystone_3557,Through-hole,"3 clips per position; CH3 5 A; AUTO: fuse in COM-SW; BYPASS: fuse in COM-LOAD,3 clips per position; CH4 5 A; AUTO: fuse in COM-SW; BYPASS: fuse in COM-LOAD,3 clips per position; CH5 5 A; AUTO: fuse in COM-SW; BYPASS: fuse in COM-LOAD,3 clips per position; CH6 5 A; AUTO: fuse in COM-SW; BYPASS: fuse in COM-LOAD,3 clips per position; CH7 5 A; AUTO: fuse in COM-SW; BYPASS: fuse in COM-LOAD"
20,F8,1,Keystone Electronics,3557,ATO 20A,Fuseholder_ATO_3pos_Keystone_3557,Through-hole,3 clips per position; CH8 20 A; AUTO: fuse in COM-SW; BYPASS: fuse in COM-LOAD
21,F9,1,Littelfuse,0466002.NR,2A 1206,1206,SMD,logic supply fuse
22,"H1,H2,H3,H4",4,,,M3,MountingHole_3.2mm_M3,Through-hole,
23,J1,1,Wurth Elektronik,691311400116,Wuerth 691311400116,TerminalBlock_1x16_P7.62mm_Wuerth_3114,Through-hole,"odd pins = GND, even pins = LOAD+"
24,J2,1,Keystone Electronics,8196,+12V IN,ScrewTerminal_Keystone_8196_10-32,Through-hole,
25,J3,1,Keystone Electronics,8196,GND IN,ScrewTerminal_Keystone_8196_10-32,Through-hole,
26,J4,1,GCT,USB4105-GF-A,USB-C,USB_C_Receptacle_GCT_USB4105-xx-A_16P_TopMnt_Horizontal,SMD,
27,J5,1,Wurth Elektronik,61300411121,UART,PinHeader_1x04_P2.54mm_Vertical,Through-hole,GND 3V3 TX RX
28,L1,1,Bourns,SRP7028A-100M,10uH 4A,L_Bourns_SRP7028A_7.3x6.6mm,SMD,
29,R1,1,YAGEO,RC0603FR-07200KL,200k 1%,0603,SMD,fsw 500 kHz
30,R2,1,YAGEO,RC0603FR-0731K6L,31.6k 1%,0603,SMD,
31,R3,1,YAGEO,RC0603FR-0710K2L,10.2k 1%,0603,SMD,
32,R4,1,YAGEO,RC0603FR-073K9L,3.9k,0603,SMD,
33,"R5,R6",2,YAGEO,RC0603FR-0710KL,10k,0603,SMD,
34,"R7,R8",2,YAGEO,RC0603FR-075K1L,5.1k,0603,SMD,
35,R9,1,YAGEO,RC0603FR-071KL,1k,0603,SMD,
36,"R101,R102,R105,R201,R202,R205,R301,R302,R305,R401,R402,R405,R501,R502,R505,R601,R602,R605,R701,R702,R705,R801,R802,R805",24,YAGEO,RC0603FR-074K7L,4.7k,0603,SMD,"RADC,RDEN,RIN"
37,"R103,R203,R303,R403,R503,R603,R703,R803",8,YAGEO,RC0805FR-0747RL,47R,0805,SMD,RGND (ReverseON)
38,"R104,R204",2,YAGEO,RC0603FR-072K2L,2.2k 1%,0603,SMD,RSENSE
39,"R106,R206,R306,R406,R506,R606,R706,R806",8,YAGEO,RC0603FR-0747KL,47k,0603,SMD,RPD
40,"R107,R207,R307,R407,R507,R607,R707,R807",8,YAGEO,RC0603FR-072K2L,2.2k,0603,SMD,RLED
41,"R304,R404,R504,R604,R704",5,YAGEO,RC0603FR-073K3L,3.3k 1%,0603,SMD,RSENSE
42,R804,1,YAGEO,RC0603FR-071K2L,1.2k 1%,0603,SMD,RSENSE
43,SW1,1,C&K,PTS645SM43SMTR92,RESET,SW_SPST_PTS645Sx43SMTR92,SMD,
44,SW2,1,C&K,PTS645SM43SMTR92,BOOT,SW_SPST_PTS645Sx43SMTR92,SMD,
45,"U1,U2",2,Infineon,BTS70041EPPXUMA1,BTS7004-1EPP,Infineon_PG-TSDSO-14-22,SMD,"CH1 10 A,CH2 10 A"
46,"U3,U4,U5,U6,U7",5,Infineon,BTS70081EPRXUMA1,BTS7008-1EPP,Infineon_PG-TSDSO-14-22,SMD,"CH3 5 A,CH4 5 A,CH5 5 A,CH6 5 A,CH7 5 A"
47,U8,1,Infineon,BTS70021EPPXUMA1,BTS7002-1EPP,Infineon_PG-TSDSO-14-22,SMD,CH8 20 A
48,U9,1,Texas Instruments,TPS54360BDDAR,TPS54360B,TI_SO-PowerPAD-8_ThermalVias,SMD,
49,U10,1,Espressif,ESP32-S3-WROOM-1-N8,ESP32-S3-WROOM-1-N8,ESP32-S3-WROOM-1,SMD,
50,U11,1,STMicroelectronics,USBLC6-2SC6,USBLC6-2SC6,SOT-23-6,SMD,
